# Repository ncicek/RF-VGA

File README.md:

# RF-VGA
A handy RF amplifier/attenuator tool for the lab. Based on a Hittite HMC625B.

- Frequency: 50MHz to 4GHz (see response plots below for roll off)
- Approximate gain / attenuation range: -10dB to +20dB
- Max input power: 11dBm
- Max output power: 16dBm (1dB compression point)

# Render:

# Board photo:

# VNA characterization results:

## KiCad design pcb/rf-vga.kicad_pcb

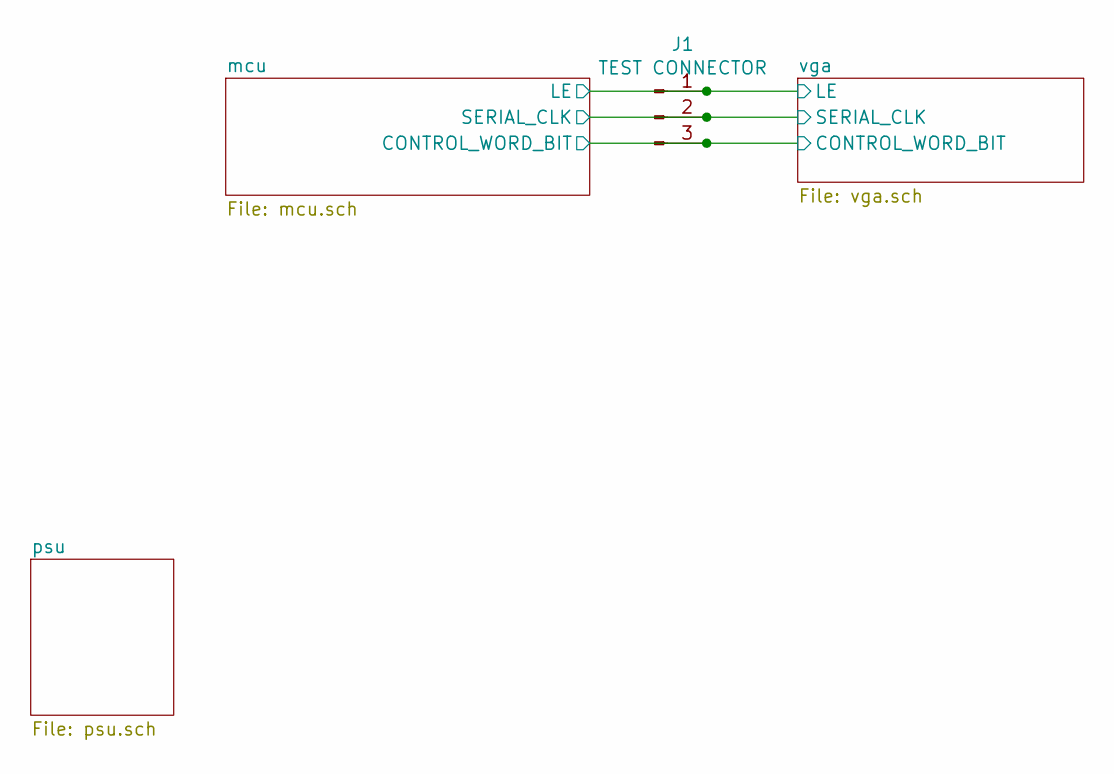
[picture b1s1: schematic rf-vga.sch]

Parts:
J1: TEST CONNECTOR; PinHeader_1x03_P2.54mm_Vertical

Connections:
/mcu/CONTROL_WORD_BIT: J1.3; also elsewhere on the board
/mcu/LE: J1.1; also elsewhere on the board
/mcu/SERIAL_CLK: J1.2; also elsewhere on the board

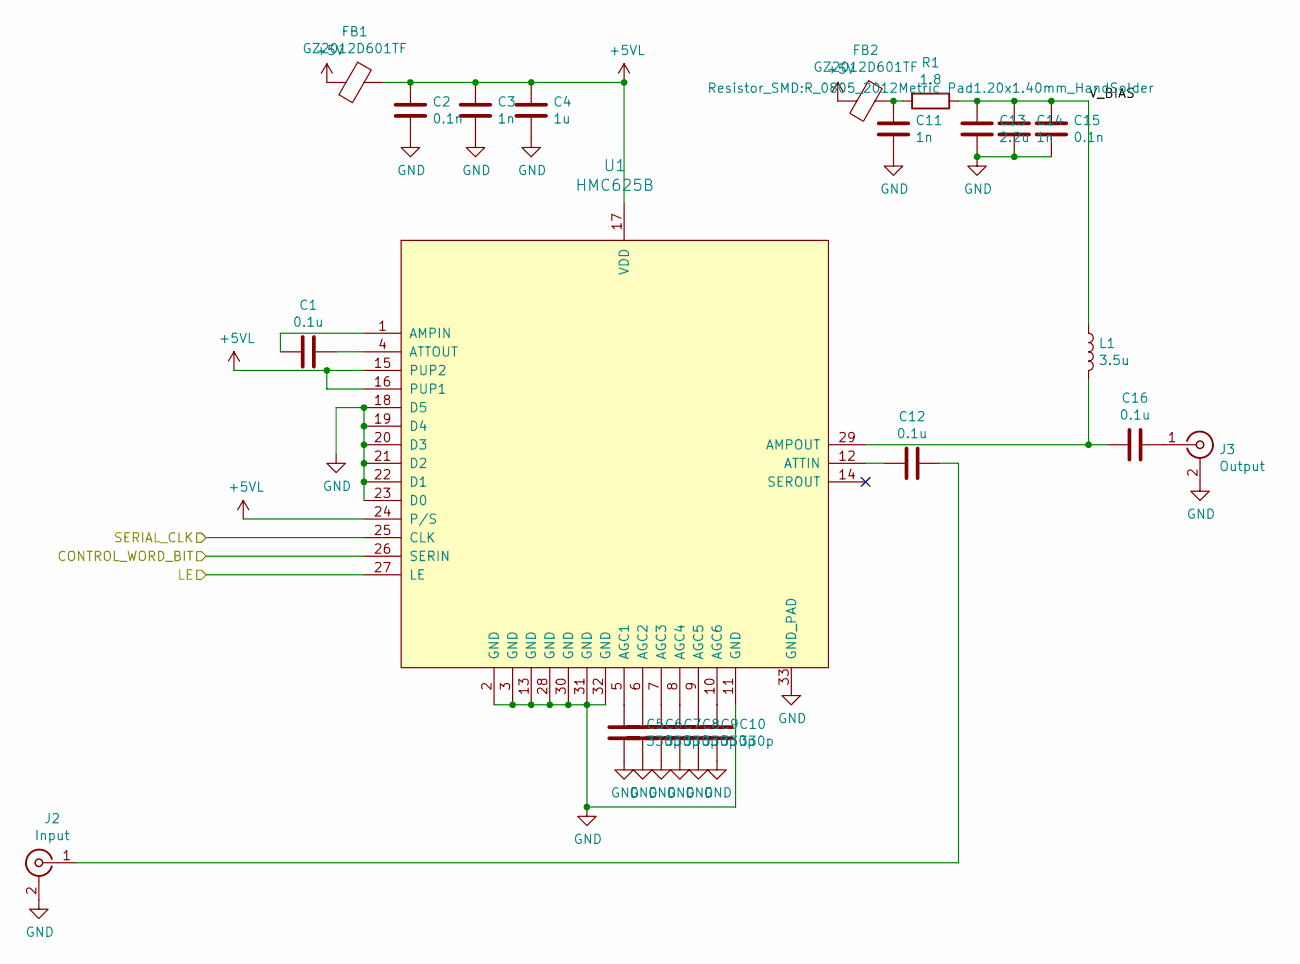
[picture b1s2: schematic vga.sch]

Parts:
C1, C12, C16: 0.1u; C_0402_1005Metric
C2, C15: 0.1n; C_0402_1005Metric
C3, C11, C14: 1n; C_0402_1005Metric
C4: 1u; C_0402_1005Metric
C5, C6, C7, C8, C9, C10: 330p; C_0402_1005Metric
C13: 2.2u; C_0402_1005Metric
FB1, FB2: GZ2012D601TF; L_0805_2012Metric
J2: Input; SMA_Samtec_SMA-J-P-X-ST-EM1_EdgeMount_withSTEP
J3: Output; SMA_Samtec_SMA-J-P-X-ST-EM1_EdgeMount_withSTEP
L1: 3.5u; 4310LC
R1: 1.8; R_0805_2012Metric_Pad1.20x1.40mm_HandSolder
U1: HMC625B; QFN-32-1EP_5x5mm_P0.5mm_EP3.45x3.45mm_ThermalVias

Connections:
+5V: FB1.2, FB2.2; also elsewhere on the board
+5VL: C2.1, C3.1, C4.1, FB1.1, U1.15 (PUP2), U1.16 (PUP1), U1.17 (VDD), U1.24 (P/S)
/mcu/CONTROL_WORD_BIT: U1.26 (SERIN); also elsewhere on the board
/mcu/LE: U1.27 (LE); also elsewhere on the board
/mcu/SERIAL_CLK: U1.25 (CLK); also elsewhere on the board
/vga/V_BIAS: C13.1, C14.1, C15.1, L1.1, R1.1
GND: C2.2, C3.2, C4.2, C5.2, C6.2, C7.2, C8.2, C9.2, C10.2, C11.2, C13.2, C14.2, C15.2, J2.2 (Ext), J3.2 (Ext), U1.2 (GND), U1.3 (GND), U1.11 (GND), U1.13 (GND), U1.18 (D5), U1.19 (D4), U1.20 (D3), U1.21 (D2), U1.22 (D1), U1.23 (D0), U1.28 (GND), U1.30 (GND), U1.31 (GND), U1.32 (GND), U1.33 (GND_PAD); also elsewhere on the board
unnamed: C1.1, U1.4 (ATTOUT)
unnamed: C1.2, U1.1 (AMPIN)
unnamed: C5.1, U1.5 (AGC1)
unnamed: C6.1, U1.6 (AGC2)
unnamed: C7.1, U1.7 (AGC3)
unnamed: C8.1, U1.8 (AGC4)
unnamed: C9.1, U1.9 (AGC5)
unnamed: C10.1, U1.10 (AGC6)
unnamed: C11.1, FB2.1, R1.2
unnamed: C12.1, J2.1 (In)
unnamed: C12.2, U1.12 (ATTIN)
unnamed: C16.1, J3.1 (In)
unnamed: C16.2, L1.2, U1.29 (AMPOUT)

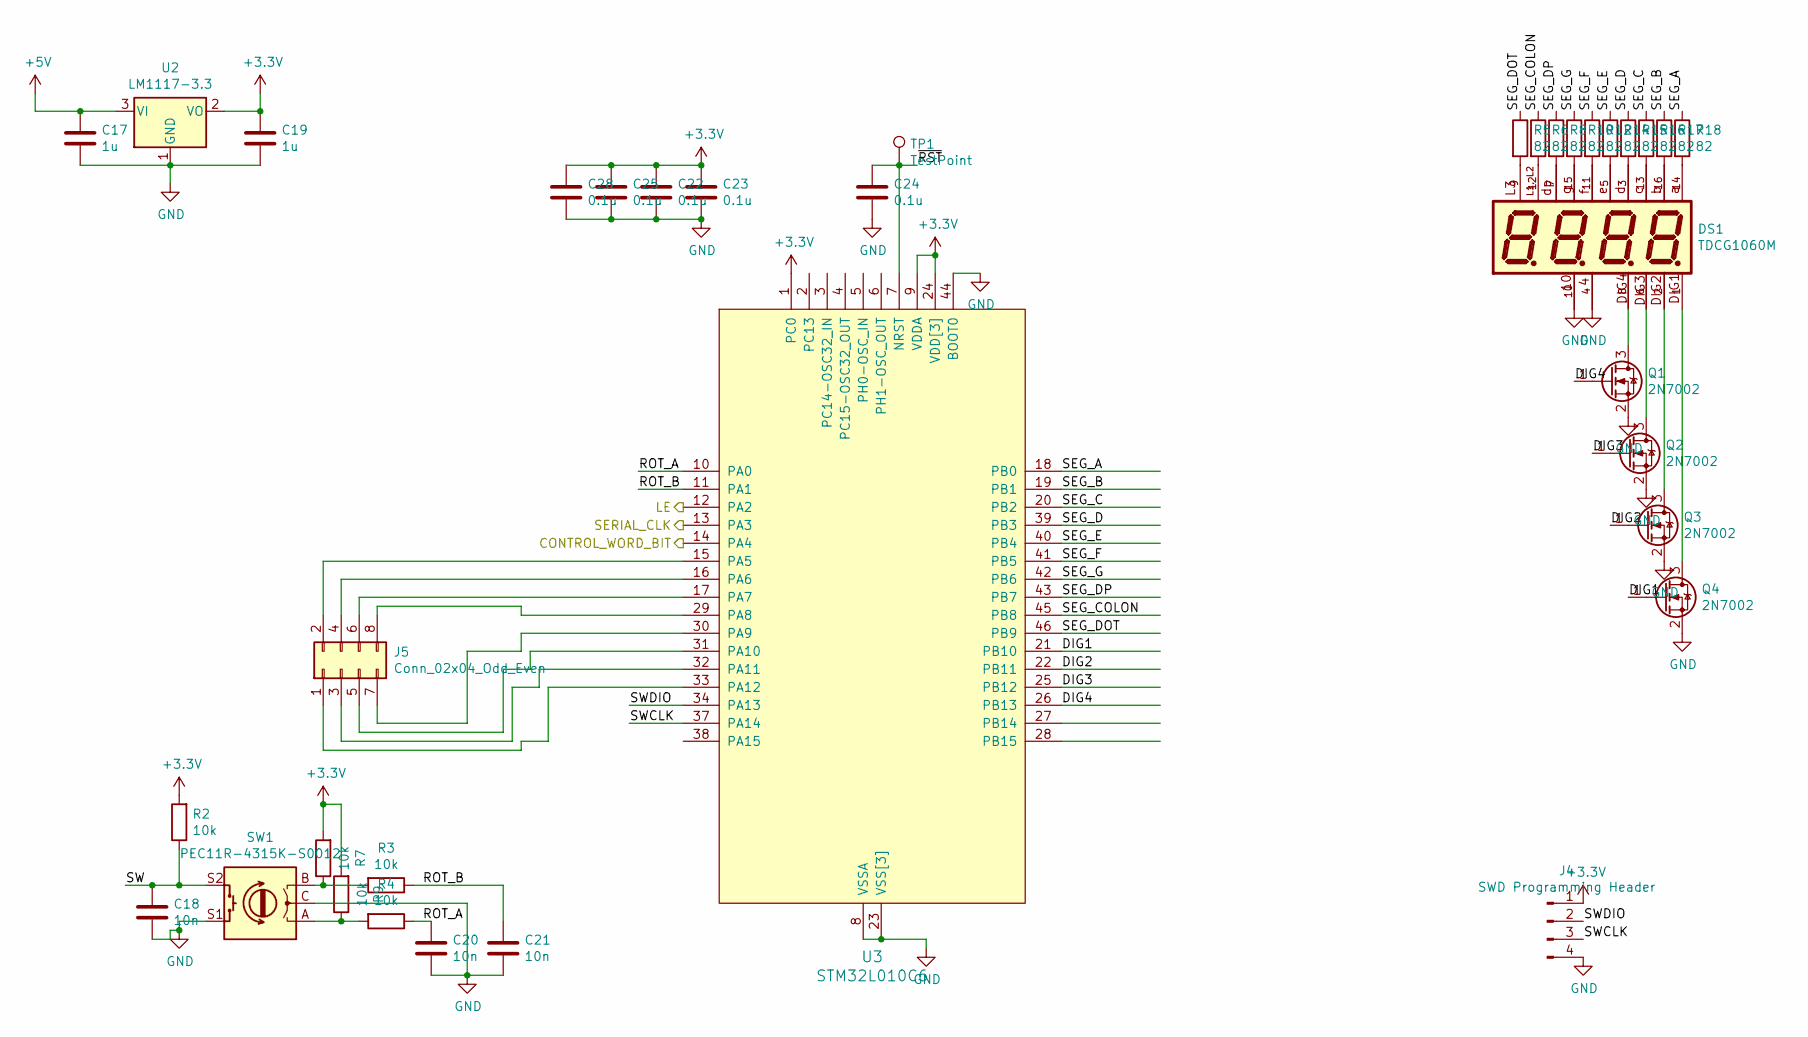
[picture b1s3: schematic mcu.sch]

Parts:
C17, C19: 1u; C_0402_1005Metric
C18, C20, C21: 10n; C_0402_1005Metric
C22, C23, C24, C25, C28: 0.1u; C_0402_1005Metric
DS1: TDCG1060M; DISPLAY_TDCG1060M; PARTREV 1.7
J4: SWD Programming Header; PinHeader_1x04_P2.54mm_Vertical
J5: Conn_02x04_Odd_Even; PinHeader_2x04_P2.54mm_Vertical
Q1, Q2, Q3, Q4: 2N7002; SOT-23
R2, R3, R4, R7, R9: 10k; R_0402_1005Metric
R5, R6, R8, R10, R12, R14, R15, R16, R17, R18: 82; R_0402_1005Metric
SW1: PEC11R-4315K-S0012; RotaryEncoder_Alps_EC11E-Switch_Vertical_H20mm_CircularMoun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
TP1: TestPoint; TestPoint_Pad_2.0x2.0mm
U2: LM1117-3.3; SOT-223-3_TabPin2
U3: ﻿STM32L010C6; LQFP-48_7x7mm_P0.5mm

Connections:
+3V3: C19.1, C22.1, C23.1, C25.1, C28.1, J4.1, R2.2, R7.2, R9.2, U2.2 (VO), U3.1 (PC0), U3.9 (VDDA), U3.24 (VDD[3]), U3.36 (VDD[3]), U3.48 (VDD[3])
+5V: C17.1, U2.3 (VI); also elsewhere on the board
/mcu/CONTROL_WORD_BIT: U3.14 (PA4); also elsewhere on the board
/mcu/DIG1: Q4.1 (G), U3.21 (PB10)
/mcu/DIG2: Q3.1 (G), U3.22 (PB11)
/mcu/DIG3: Q2.1 (G), U3.25 (PB12)
/mcu/DIG4: Q1.1 (G), U3.26 (PB13)
/mcu/LE: U3.12 (PA2); also elsewhere on the board
/mcu/ROT_A: C20.1, R4.1, U3.10 (PA0)
/mcu/ROT_B: C21.1, R3.1, U3.11 (PA1)
/mcu/SEG_A: R18.1, U3.18 (PB0)
/mcu/SEG_B: R17.1, U3.19 (PB1)
/mcu/SEG_C: R16.1, U3.20 (PB2)
/mcu/SEG_COLON: R6.1, U3.45 (PB8)
/mcu/SEG_D: R15.1, U3.39 (PB3)
/mcu/SEG_DOT: R5.1, U3.46 (PB9)
/mcu/SEG_DP: R8.1, U3.43 (PB7)
/mcu/SEG_E: R14.1, U3.40 (PB4)
/mcu/SEG_F: R12.1, U3.41 (PB5)
/mcu/SEG_G: R10.1, U3.42 (PB6)
/mcu/SERIAL_CLK: U3.13 (PA3); also elsewhere on the board
/mcu/SW: C18.1, R2.1, SW1.S2
/mcu/SWCLK: J4.3, U3.37 (PA14)
/mcu/SWDIO: J4.2, U3.34 (PA13)
/mcu/~RST: C24.1, TP1.1, U3.7 (NRST)
GND: C17.2, C18.2, C19.2, C20.2, C21.2, C22.2, C23.2, C24.2, C25.2, C28.2, DS1.4, DS1.10, J4.4, Q1.2 (S), Q2.2 (S), Q3.2 (S), Q4.2 (S), SW1.C, SW1.S1, U2.1 (GND), U3.8 (VSSA), U3.23 (VSS[3]), U3.35 (VSS[3]), U3.44 (BOOT0), U3.47 (VSS[3]); also elsewhere on the board
unnamed: DS1.1, Q4.3 (D)
unnamed: DS1.2, Q3.3 (D)
unnamed: DS1.3, R15.2
unnamed: DS1.5, R14.2
unnamed: DS1.6, Q2.3 (D)
unnamed: DS1.7, R8.2
unnamed: DS1.8, Q1.3 (D)
unnamed: DS1.9, R5.2
unnamed: DS1.11, R12.2
unnamed: DS1.12, R6.2
unnamed: DS1.13, R16.2
unnamed: DS1.14, R18.2
unnamed: DS1.15, R10.2
unnamed: DS1.16, R17.2
unnamed: J5.1, U3.33 (PA12)
unnamed: J5.2, U3.15 (PA5)
unnamed: J5.3, U3.32 (PA11)
unnamed: J5.4, U3.16 (PA6)
unnamed: J5.5, U3.31 (PA10)
unnamed: J5.6, U3.17 (PA7)
unnamed: J5.7, U3.30 (PA9)
unnamed: J5.8, U3.29 (PA8)
unnamed: R3.2, R7.1, SW1.B
unnamed: R4.2, R9.1, SW1.A

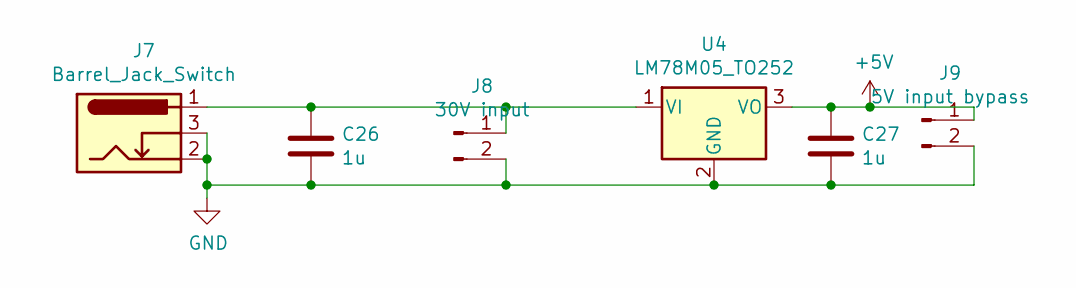
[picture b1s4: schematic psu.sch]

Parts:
C26, C27: 1u; C_0402_1005Metric
J7: Barrel_Jack_Switch; BarrelJack_Horizontal
J8: 30V input; PinHeader_1x02_P2.54mm_Vertical
J9: 5V input bypass; PinHeader_1x02_P2.54mm_Vertical
U4: LM78M05_TO252; TO-252-2

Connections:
+5V: C27.1, J9.1, U4.3 (VO); also elsewhere on the board
GND: C26.2, C27.2, J7.2, J7.3, J8.2, J9.2, U4.2 (GND); also elsewhere on the board
unnamed: C26.1, J7.1, J8.1, U4.1 (VI)

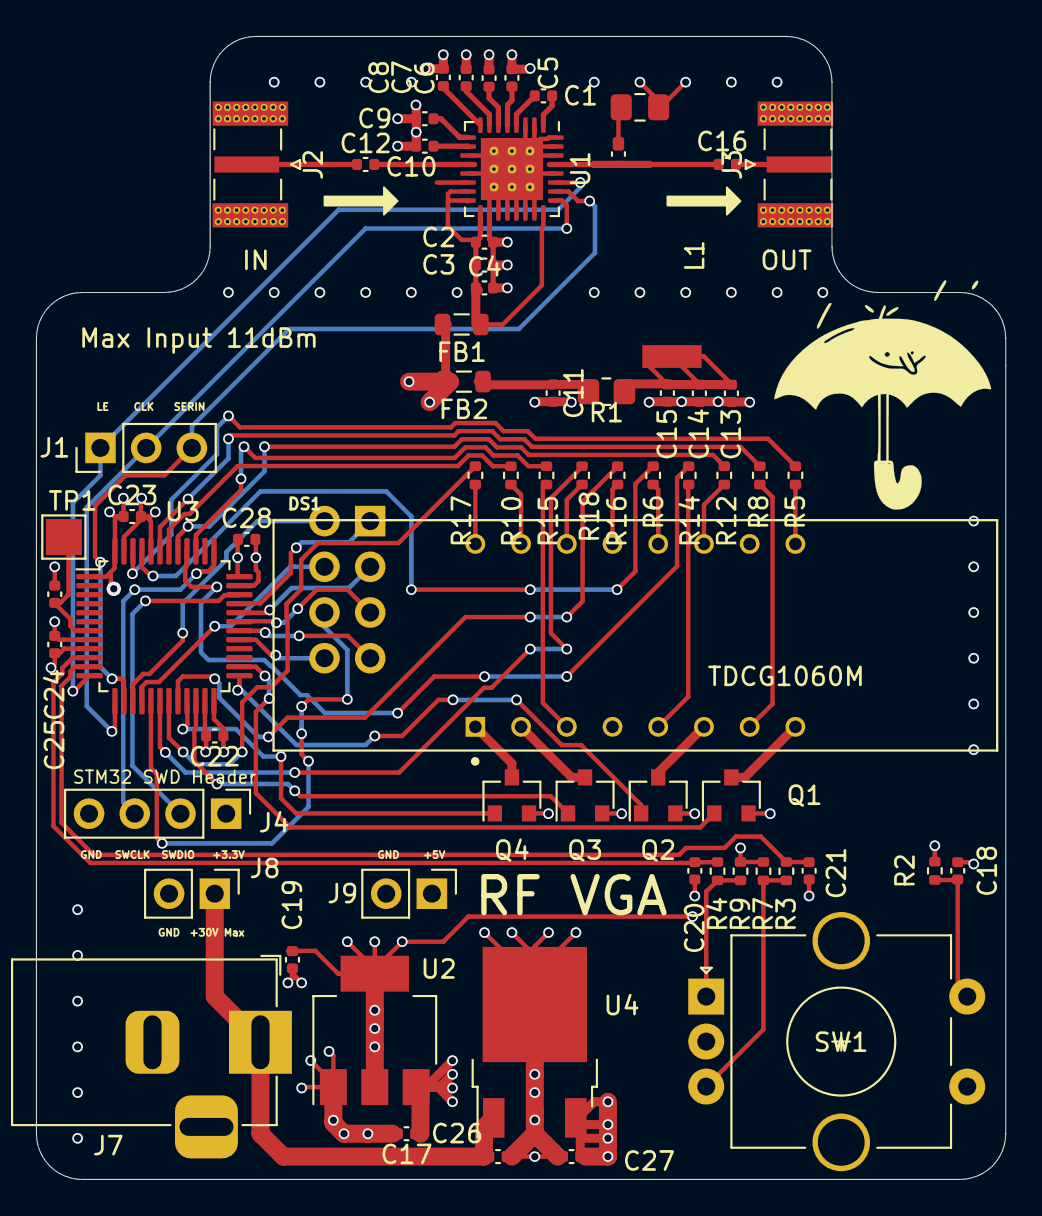
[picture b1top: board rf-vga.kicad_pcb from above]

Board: 4 copper layers, 53.8 x 63.5 mm, 66 parts (1 on the bottom side), 66 nets.

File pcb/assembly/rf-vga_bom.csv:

Comment,Designator,Footprint,LCSC
0.1u,"C1,C12,C16,C22,C23,C24,C25,C28",Capacitor_SMD:C_0402_1005Metric,C1525
2.2u,C13,Capacitor_SMD:C_0402_1005Metric,C23733
0.1n,"C2,C15",Capacitor_SMD:C_0402_1005Metric,C1546
10n,"C18,C20,C21",Capacitor_SMD:C_0402_1005Metric,C15195
1n,"C3,C11,C14",Capacitor_SMD:C_0402_1005Metric,C1523
1u,"C4,C17,C19,C26,C27",Capacitor_SMD:C_0402_1005Metric,C52923
330p,"C5,C6,C7,C8,C9,C10",Capacitor_SMD:C_0402_1005Metric,C13533
TDCG1060M,DS1,parts:DISPLAY_TDCG1060M,
GZ2012D601TF,"FB1,FB2",Inductor_SMD:L_0805_2012Metric,C1017
TEST CONNECTOR,J1,Connector_PinHeader_2.54mm:PinHeader_1x03_P2.54mm_Vertical,
Input,J2,parts:SMA_Samtec_SMA-J-P-X-ST-EM1_EdgeMount_withSTEP,
Output,J3,parts:SMA_Samtec_SMA-J-P-X-ST-EM1_EdgeMount_withSTEP,
SWD Programming Header,J4,Connector_PinHeader_2.54mm:PinHeader_1x04_P2.54mm_Vertical,
Conn_02x04_Odd_Even,J5,Connector_PinHeader_2.54mm:PinHeader_2x04_P2.54mm_Vertical,
Barrel_Jack_Switch,J7,Connector_BarrelJack:BarrelJack_Horizontal,
30V input,J8,Connector_PinHeader_2.54mm:PinHeader_1x02_P2.54mm_Vertical,
5V input bypass,J9,Connector_PinHeader_2.54mm:PinHeader_1x02_P2.54mm_Vertical,
3.5u,L1,4310LC:4310LC,
2N7002,"Q1,Q2,Q3,Q4",Package_TO_SOT_SMD:SOT-23,C20917
1.8,R1,Resistor_SMD:R_0402_1005Metric,
10k,"R2,R3,R4,R7,R9",Resistor_SMD:R_0402_1005Metric,C25744
82,"R5,R6,R8,R10,R12,R14,R15,R16,R17,R18",Resistor_SMD:R_0402_1005Metric,C25076
Rotary_Encoder_Switch,SW1,Rotary_Encoder:RotaryEncoder_Alps_EC11E-Switch_Vertical_H20mm_CircularMountingHoles,
TestPoint,TP1,TestPoint:TestPoint_Pad_2.0x2.0mm,
HMC625B,U1,Package_DFN_QFN:QFN-32-1EP_5x5mm_P0.5mm_EP3.45x3.45mm_ThermalVias,
LM1117-3.3,U2,Package_TO_SOT_SMD:SOT-223-3_TabPin2,C6186
STM32L010C6,U3,Package_QFP:LQFP-48_7x7mm_P0.5mm,C2802165
LM78M05_TO252,U4,Package_TO_SOT_SMD:TO-252-2,C58069

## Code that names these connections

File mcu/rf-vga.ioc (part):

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Mcu.Name=STM32L051C(6-8)Tx
Mcu.Package=LQFP48
Mcu.UserName=STM32L051C8Tx
PA0.Signal=S_TIM2_CH1
PA1.Signal=S_TIM2_CH2
PA13.Mode=Serial_Wire
PA13.Signal=SYS_SWDIO
PA14.Mode=Serial_Wire
PA14.Signal=SYS_SWCLK
PA2.GPIOParameters=GPIO_Label
PA2.GPIO_Label=LE
PA2.Signal=GPIO_Output
PA3.GPIOParameters=GPIO_Label
PA3.GPIO_Label=SER_CLK
PA3.Signal=GPIO_Output
PA4.GPIOParameters=GPIO_Label
PA4.GPIO_Label=SER_OUT
PA4.Signal=GPIO_Output
PB0.Signal=GPIO_Output
PB1.Signal=GPIO_Output
PB10.Signal=GPIO_Output
PB11.Signal=GPIO_Output
PB12.Signal=GPIO_Output
PB13.Signal=GPIO_Output
PB2.Signal=GPIO_Output
PB3.Signal=GPIO_Output
PB4.Signal=GPIO_Output
PB5.Signal=GPIO_Output
PB6.Signal=GPIO_Output
PB7.Signal=GPIO_Output
PB8.Signal=GPIO_Output
PB9.Signal=GPIO_Output
RCC.HSE_VALUE=8000000
RCC.SYSCLKFreq_VALUE=2097000
board=custom

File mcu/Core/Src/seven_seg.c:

#include <stdint.h>
#include <stdbool.h>
#include <math.h>
#include "main.h"
#include "seven_seg.h"
#include <stdio.h>

#define SEG_A 1<<0
#define SEG_B 1<<1
#define SEG_C 1<<2
#define SEG_D 1<<3
#define SEG_E 1<<4
#define SEG_F 1<<5
#define SEG_G 1<<6
#define SEG_DP 1<<7
#define SEG_COLON 1<<8
#define SEG_DOT 1<<9
#define DIG1 1<<10
#define DIG2 1<<11
#define DIG3 1<<12
#define DIG4 1<<13

SevenSeg ss = { .current_digit = 0 };

void display_segment(uint8_t digit, char character, bool decimal_point) {
    uint16_t GPIOB_value = 0;

    const uint8_t seven_seg_map[10] = { 
                                SEG_A|SEG_B|SEG_C|SEG_D|SEG_E|SEG_F|00000,
								00000|SEG_B|SEG_C|00000|00000|00000|00000,
								SEG_A|SEG_B|00000|SEG_D|SEG_E|00000|SEG_G,
								SEG_A|SEG_B|SEG_C|SEG_D|00000|00000|SEG_G,
								00000|SEG_B|SEG_C|00000|00000|SEG_F|SEG_G,
                                SEG_A|00000|SEG_C|SEG_D|00000|SEG_F|SEG_G,
								SEG_A|00000|SEG_C|SEG_D|SEG_E|SEG_F|SEG_G,
								SEG_A|SEG_B|SEG_C|00000|00000|00000|00000,
                                SEG_A|SEG_B|SEG_C|SEG_D|SEG_E|SEG_F|SEG_G,
                                SEG_A|SEG_B|SEG_C|00000|00000|SEG_F|SEG_G,
								};
    const uint16_t digit_map[4] = {DIG1, DIG2, DIG3, DIG4};

    if (digit > 3) {
		Error_Handler();
    }

    GPIOB->ODR &= ~(DIG1 | DIG2 | DIG3 | DIG4); //turn off all digits before changing segments

    if ('0' <= character && character <= '9') { //ASCII number
        GPIOB_value |= seven_seg_map[character - 48];
    } else if (character == '-') { //ASCII -
        GPIOB_value |= SEG_G;
    } else if (character == ' ') {
    	//blank char
    } else {
        //Error_Handler();
    }
    
    if (decimal_point) {
        GPIOB_value |= SEG_DP;
    }

    GPIOB->ODR = GPIOB_value; //write the segments

    GPIOB->ODR |= digit_map[digit]; //flash the digit requested
}

void update_display(float value) {
    char string[NUM_DIGITS+1] = {0};
    uint8_t i;

    if (value == -0) {
    	value = +0; //why do i need to do this?
    }

    sprintf(string, "%2.1f", value);

    //shift right any trailing zeros
    while (string[NUM_DIGITS] == 0) {
    	for (i = NUM_DIGITS; i >= 1; i--) {
    		string[i] = string[i-1];
    	}
    	string[0] = ' ';
    }

    for (i = 0; i < NUM_DIGITS; i++) {
        if (string[i+1] == '.') {
            ss.display[i].digit = string[i];
            ss.display[i].decimal_point = true;
        } else if (string[i] == '.') {
        	ss.display[i].digit = string[i+1];
			ss.display[i].decimal_point = false;
        } else if (string[i] == 0) {
			ss.display[i].digit = ' ';
			ss.display[i].decimal_point = false;
        } else {
            ss.display[i].digit = string[i];
            ss.display[i].decimal_point = false;
        }
    }
}


void HAL_TIM_PeriodElapsedCallback(TIM_HandleTypeDef* htim)
{
    if (ss.current_digit < NUM_DIGITS) {
		display_segment(ss.current_digit, ss.display[ss.current_digit].digit, ss.display[ss.current_digit].decimal_point);
        ss.current_digit += 1;
    } else {
        ss.current_digit = 0;
    }
}

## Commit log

2021-09-04 Add STM32L010C6 mcu to pcb, allocate pins
2021-09-04 remove csv from git ignore, add kipart source
2021-09-04 Add STM32 kipart source
2021-09-04 add 7seg display datasheet
2021-09-12 PCB updates
2021-09-14 layout check in
2021-09-16 Completed PCB layout
2021-09-23 final tweaks and produce outputs for jlcpcb fabrication
2021-10-21 Enable encoder input
2021-10-21 Enable serial interface to vga chip
2021-10-22 began seven segment display handler
2021-10-26 Enable seven segment display
2021-12-13 Made a 3d printed case
2021-12-13 Add README
2022-01-20 Fix seven seg display issues
2022-01-20 Enclosure updates
2022-01-21 Reduce di/dt due to seven segment switching
2022-01-21 Add CMSIS
2022-01-21 Update seven segment timers for reduced di/dt
2022-01-21 Create LICENSE
2022-01-22 Startup at lowest output power
2022-01-22 Add VNA measurements, touchstone files, plots
2022-10-22 Move firmware to platformio
